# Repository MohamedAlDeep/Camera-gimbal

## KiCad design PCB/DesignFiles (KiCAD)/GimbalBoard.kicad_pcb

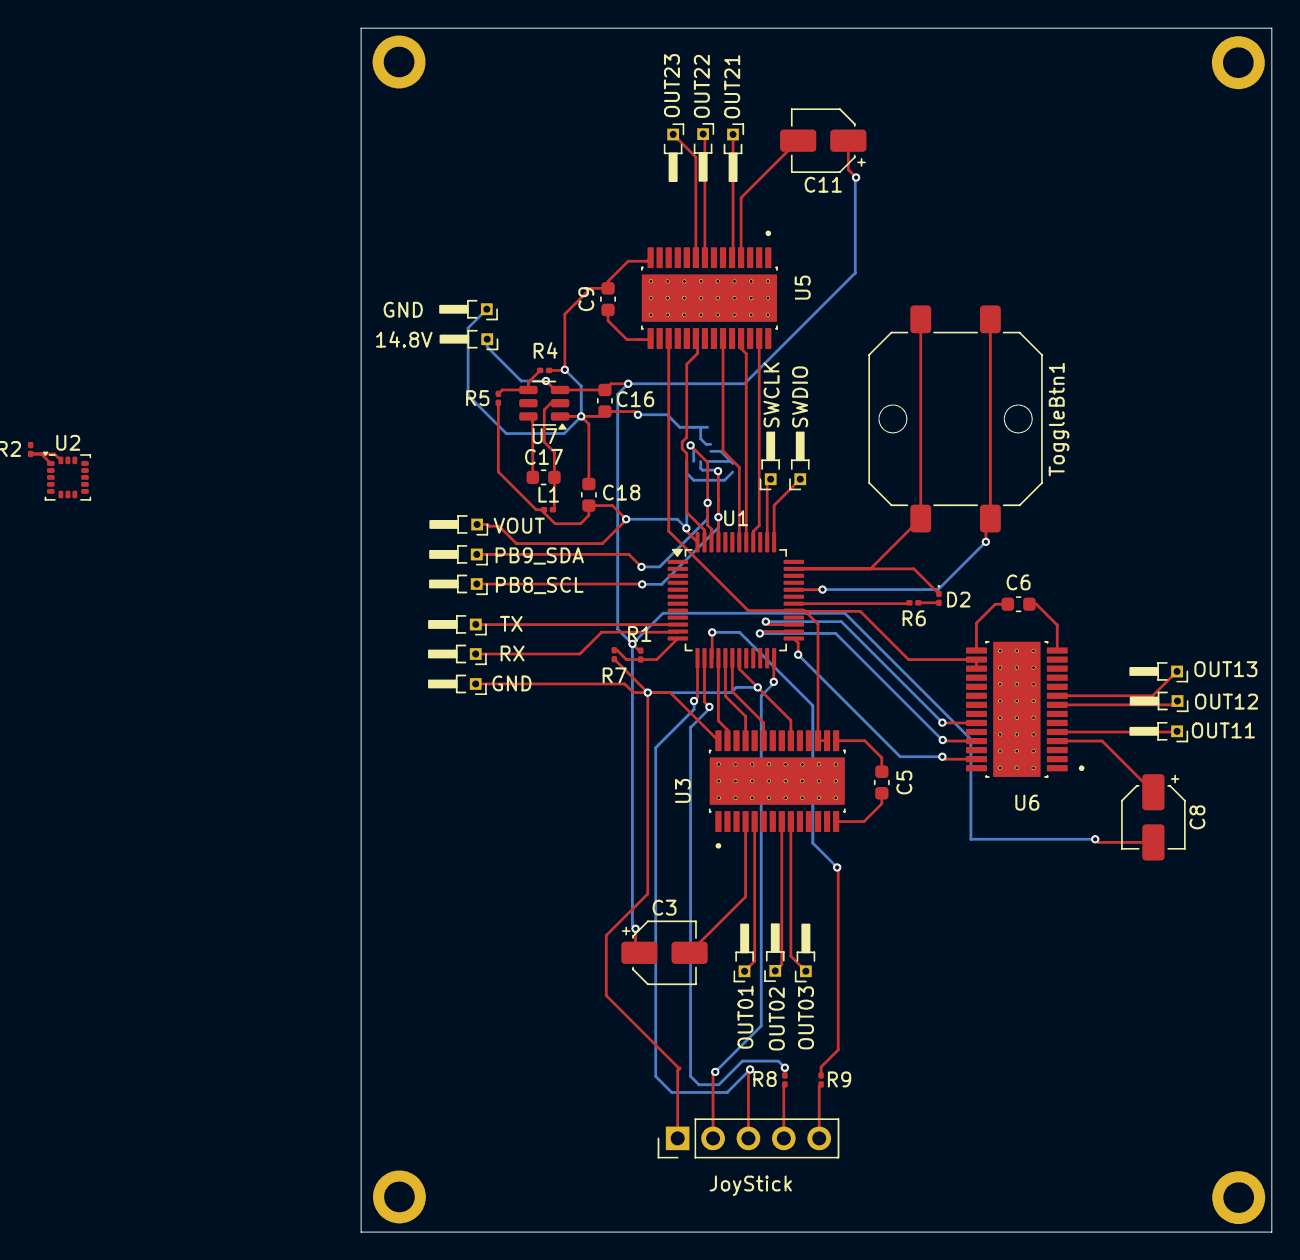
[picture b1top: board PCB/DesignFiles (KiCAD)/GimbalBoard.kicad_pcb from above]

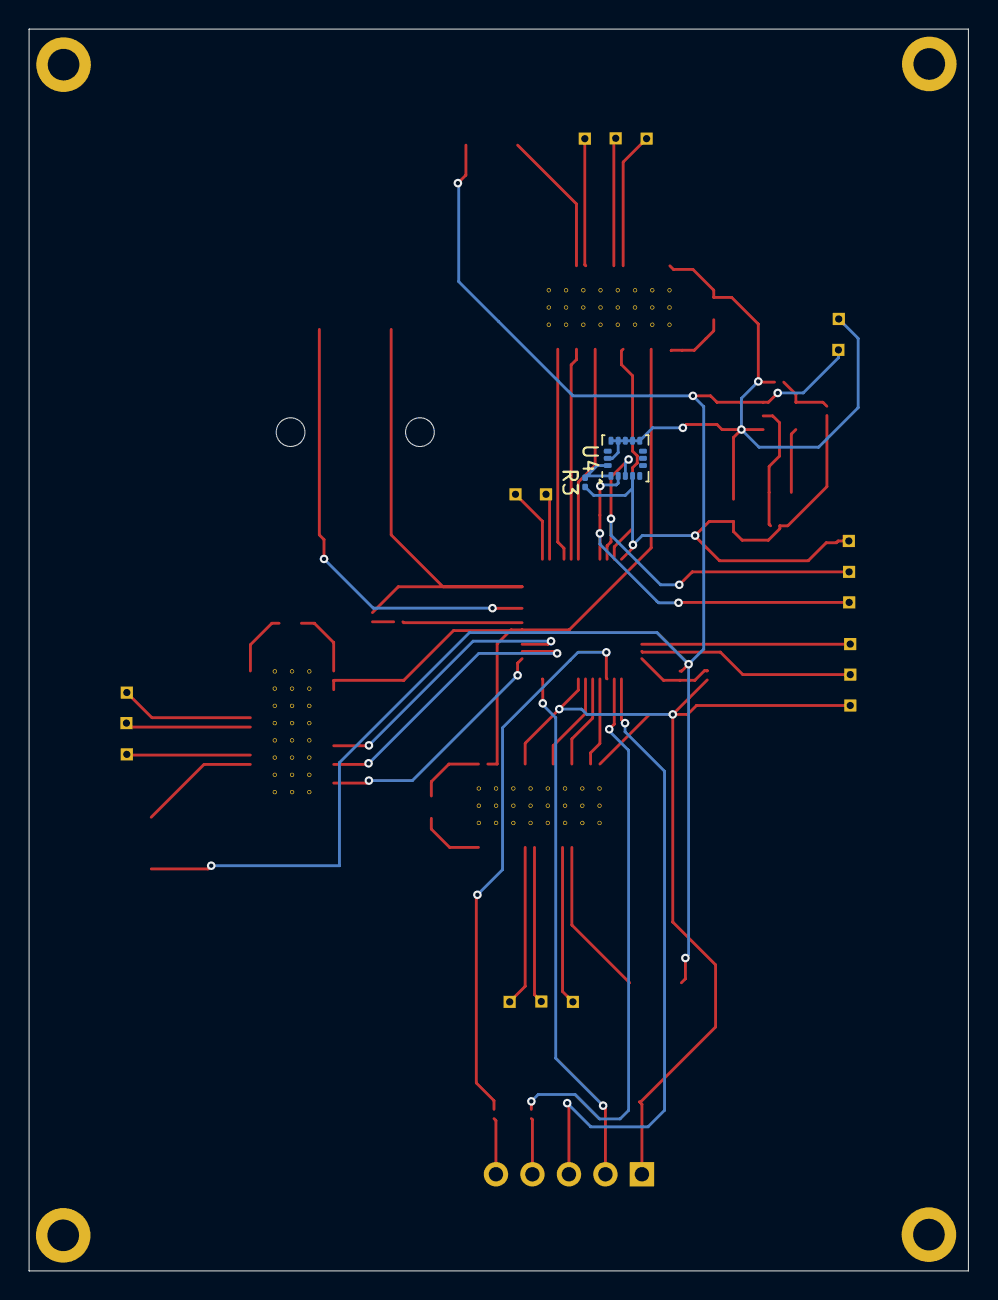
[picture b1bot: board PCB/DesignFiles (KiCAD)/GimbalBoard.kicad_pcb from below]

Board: 2 copper layers, 65.4 x 86.4 mm, 48 parts (2 on the bottom side), 46 nets.

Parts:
14.8V: TX; PinHeader_1x01_P1.00mm_Horizontal
C3, C8, C11: 100μF; CP_Elec_4x3
C5, C6, C9: 0.1μF; C_0603_1608Metric
C16, C17, C18: 10μF; C_0603_1608Metric
D2: LED; LED_0201_0603Metric
GND: RX; PinHeader_1x01_P1.00mm_Horizontal
GND#2: TX; PinHeader_1x01_P1.00mm_Horizontal
JoyStick: Conn_01x05_Pin; PinHeader_1x05_P2.54mm_Vertical
L1: 10μH; L_0201_0603Metric
OUT01, OUT11, OUT21: OUT1; PinHeader_1x01_P1.00mm_Horizontal
OUT02, OUT12, OUT22: OUT2; PinHeader_1x01_P1.00mm_Horizontal
OUT03, OUT13, OUT23: OUT3; PinHeader_1x01_P1.00mm_Horizontal
PB8_SCL: RX; PinHeader_1x01_P1.00mm_Horizontal
PB9_SDA: TX; PinHeader_1x01_P1.00mm_Horizontal
R1: 100KΩ; R_0201_0603Metric
R2, R3: 2.2KΩ; R_0201_0603Metric
R4, R7: 10KΩ; R_0201_0603Metric
R5: 45.3KΩ; R_0201_0603Metric
R6, R8, R9: 1KΩ; R_0201_0603Metric
RX: RX; PinHeader_1x01_P1.00mm_Horizontal
SWCLK: SWCLK; PinHeader_1x01_P1.00mm_Horizontal
SWDIO: SWDIO; PinHeader_1x01_P1.00mm_Horizontal
TX: TX; PinHeader_1x01_P1.00mm_Horizontal
ToggleBtn1: SW_Push; SW_Push_1P1T_NO_CK_PTS125Sx85PSMTR
U1: STM32G431CBTx; LQFP-48_7x7mm_P0.5mm
U2, U4: ICM-20602; LGA-16_3x3mm_P0.5mm_LayoutBorder3x5y
U3, U5, U6: DRV8313PWP; SOP65P640X120-29N
U7: TPS54302; SOT-23-6
VOUT: TX; PinHeader_1x01_P1.00mm_Horizontal

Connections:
GND: C5.1, C6.1, C9.1, C16.2, C18.2, D2.1 (K), GND.1, GND#2.1, JoyStick.1, R4.2, R7.2, ToggleBtn1.2, U1.19 (VSSA), U1.23 (VSS), U1.35 (VSS), U1.47 (VSS), U2.4 (SAO/SD0), U2.9 (GND), U2.10 (GND), U2.11 (GND), U2.12 (GND), U2.13 (GND), U2.15 (GND), U3.14 (GND), U3.20 (GND), U3.28 (GND), U4.9 (GND), U4.10 (GND), U4.11 (GND), U4.12 (GND), U4.13 (GND), U4.15 (GND), U5.14 (GND), U5.20 (GND), U5.28 (GND), U6.14 (GND), U6.20 (GND), U6.28 (GND), U7.1 (GND)
NSLEEP: U1.29 (PB15), U3.16 (~RESET), U3.17 (~SLEEP), U5.16 (~RESET), U5.17 (~SLEEP), U6.16 (~RESET), U6.17 (~SLEEP)
unnamed: D2.2 (A), R6.2
unnamed: TX.1, U1.10 (PA2)
unnamed: RX.1, U1.11 (PA3)
unnamed: SWDIO.1, U1.37 (PA13)
unnamed: SWCLK.1, U1.38 (PA14)
unnamed: JoyStick.4, R8.1
unnamed: JoyStick.5, R9.1
unnamed: OUT01.1, U3.5 (OUT1)
unnamed: OUT02.1, U3.8 (OUT2)
unnamed: OUT03.1, U3.9 (OUT3)
unnamed: OUT11.1, U6.5 (OUT1)
unnamed: OUT12.1, U6.8 (OUT2)
unnamed: OUT13.1, U6.9 (OUT3)
unnamed: OUT21.1, U5.5 (OUT1)
unnamed: OUT22.1, U5.8 (OUT2)
unnamed: OUT23.1, U5.9 (OUT3)
unnamed: R1.2, R7.1, U1.12 (PA4)
unnamed: R6.1, U1.30 (PA8)
unnamed: R2.2, U2.1 (VDDIO), U2.16 (VDD)
unnamed: C5.2, U3.15 (V3P3)
unnamed: R3.2, U4.1 (VDDIO), U4.16 (VDD)
unnamed: C9.2, U5.15 (V3P3)
unnamed: C6.2, U6.15 (V3P3)
unnamed: C17.1, U7.6 (BOOT)
unnamed: R4.1, R5.2, U7.4 (FB)
unnamed: C17.2, L1.1, U7.2 (SW)
PB8_SCL: PB8_SCL.1, U1.45 (PB8), U2.2 (SCL/SPC), U4.2 (SCL/SPC)
PB9_SDA: PB9_SDA.1, U1.46 (PB9), U2.3 (SDA/SDI), U4.3 (SDA/SDI)
SW_STICK: JoyStick.3, U1.13 (PA5)
TIM1_0: U1.16 (PB0), U3.27 (IN1)
TIM1_1: U1.17 (PB1), U3.25 (IN2)
TIM1_2: U1.18 (PB2), U3.23 (IN3)
TIM2_0: U1.40 (PB3), U5.27 (IN1)
TIM2_1: U1.41 (PB4), U5.25 (IN2)
TIM2_2: U1.42 (PB5), U5.23 (IN3)
TIM3_0: U1.25 (PB11), U6.27 (IN1)
TIM3_1: U1.26 (PB12), U6.25 (IN2)
TIM3_2: U1.27 (PB13), U6.23 (IN3)
Toggle: ToggleBtn1.1, U1.32 (PA10)
VIN: 14.8V.1, C3.1, C8.2, C11.1, C16.1, R1.1, U7.3 (VIN)
VM: C3.2, C8.1, C11.2, U3.4 (VM), U3.11 (VM), U5.4 (VM), U5.11 (VM), U6.4 (VM), U6.11 (VM)
VOUT: C18.1, JoyStick.2, L1.2, R2.1, R3.1, R5.1, U1.21 (VDDA), U1.24 (VDD), U1.36 (VDD), U1.48 (VDD), U4.4 (SAO/SD0), VOUT.1
VRx: R8.2, U1.14 (PA6)
VRy: R9.2, U1.15 (PA7)

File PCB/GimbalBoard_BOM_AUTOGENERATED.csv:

"Id";"Designator";"Footprint";"Quantity";"Designation";"Supplier and ref";
1;"R5";"R_0201_0603Metric";1;"45.3KΩ";;;
2;"D2";"LED_0201_0603Metric";1;"LED";;;
3;",";"";2;"";;;
4;"14.8V,PB9_SDA,VOUT,GND,TX";"PinHeader_1x01_P1.00mm_Horizontal";5;"TX";;;
5;"R6,R8,R9";"R_0201_0603Metric";3;"1KΩ";;;
6;"ToggleBtn1";"SW_Push_1P1T_NO_CK_PTS125Sx85PSMTR";1;"SW_Push";;;
7;"U6,U3,U5";"SOP65P640X120-29N";3;"DRV8313PWP";;;
8;"SWDIO";"PinHeader_1x01_P1.00mm_Horizontal";1;"SWDIO";;;
9;"R1";"R_0201_0603Metric";1;"100KΩ";;;
10;"R7,R4";"R_0201_0603Metric";2;"10KΩ";;;
11;"C3,C8,C11";"CP_Elec_4x3";3;"100μF";;;
12;"C16,C18,C17";"C_0603_1608Metric";3;"10μF";;;
13;"OUT23,OUT03,OUT13";"PinHeader_1x01_P1.00mm_Horizontal";3;"OUT3";;;
14;"OUT22,OUT12,OUT02";"PinHeader_1x01_P1.00mm_Horizontal";3;"OUT2";;;
15;"GND,RX,PB8_SCL";"PinHeader_1x01_P1.00mm_Horizontal";3;"RX";;;
16;"OUT11,OUT21,OUT01";"PinHeader_1x01_P1.00mm_Horizontal";3;"OUT1";;;
17;"C5,C9,C6";"C_0603_1608Metric";3;"0.1μF";;;
18;"JoyStick";"PinHeader_1x05_P2.54mm_Vertical";1;"Conn_01x05_Pin";;;
19;"SWCLK";"PinHeader_1x01_P1.00mm_Horizontal";1;"SWCLK";;;
20;"U1";"LQFP-48_7x7mm_P0.5mm";1;"STM32G431CBTx";;;
21;"L1";"L_0201_0603Metric";1;"10μH";;;
22;"U7";"SOT-23-6";1;"TPS54302";;;
23;"U4,U2";"LGA-16_3x3mm_P0.5mm_LayoutBorder3x5y";2;"ICM-20602";;;
24;"R3,R2";"R_0201_0603Metric";2;"2.2KΩ";;;

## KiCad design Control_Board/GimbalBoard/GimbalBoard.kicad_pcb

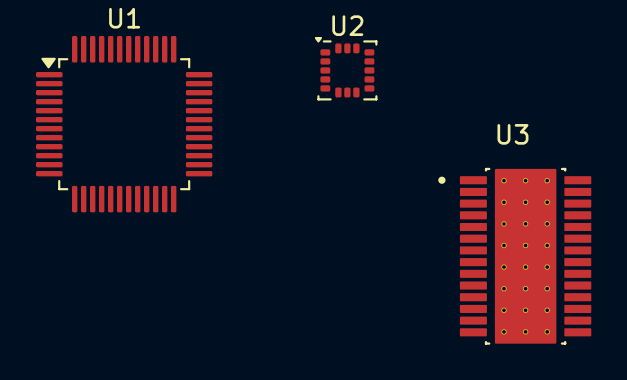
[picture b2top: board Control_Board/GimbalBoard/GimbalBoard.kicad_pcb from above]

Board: 2 copper layers, 3 parts (0 on the bottom side), 4 nets, no tracks yet.

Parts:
U1: STM32G431CBTx; LQFP-48_7x7mm_P0.5mm
U2: ICM-20602; LGA-16_3x3mm_P0.5mm_LayoutBorder3x5y
U3: DRV8313PWP; SOP65P640X120-29N

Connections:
GND: U3.14 (GND), U3.20 (GND), U3.28 (GND)
unnamed: U1.23 (VSS), U1.35 (VSS), U1.47 (VSS)
unnamed: U2.9 (GND), U2.10 (GND), U2.11 (GND), U2.12 (GND), U2.13 (GND), U2.15 (GND)
VM: U3.4 (VM), U3.11 (VM)

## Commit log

2026-01-18 Added bom and journal
2026-01-18 Touches
2026-01-18 Schematic
2026-01-18 Aditionals and Edits
2026-01-18 typo
2026-01-20 Result
2026-01-20 fix file
2026-01-20 Polished
2026-01-20 Final
2026-01-20 pcb image
2026-01-20 firmware
2026-01-20 journal total time
2026-02-02 wiring diagram
2026-02-02 edit on wiring diagram
2026-02-02 Bom edit
2026-02-03 edit to BOM & delivery
